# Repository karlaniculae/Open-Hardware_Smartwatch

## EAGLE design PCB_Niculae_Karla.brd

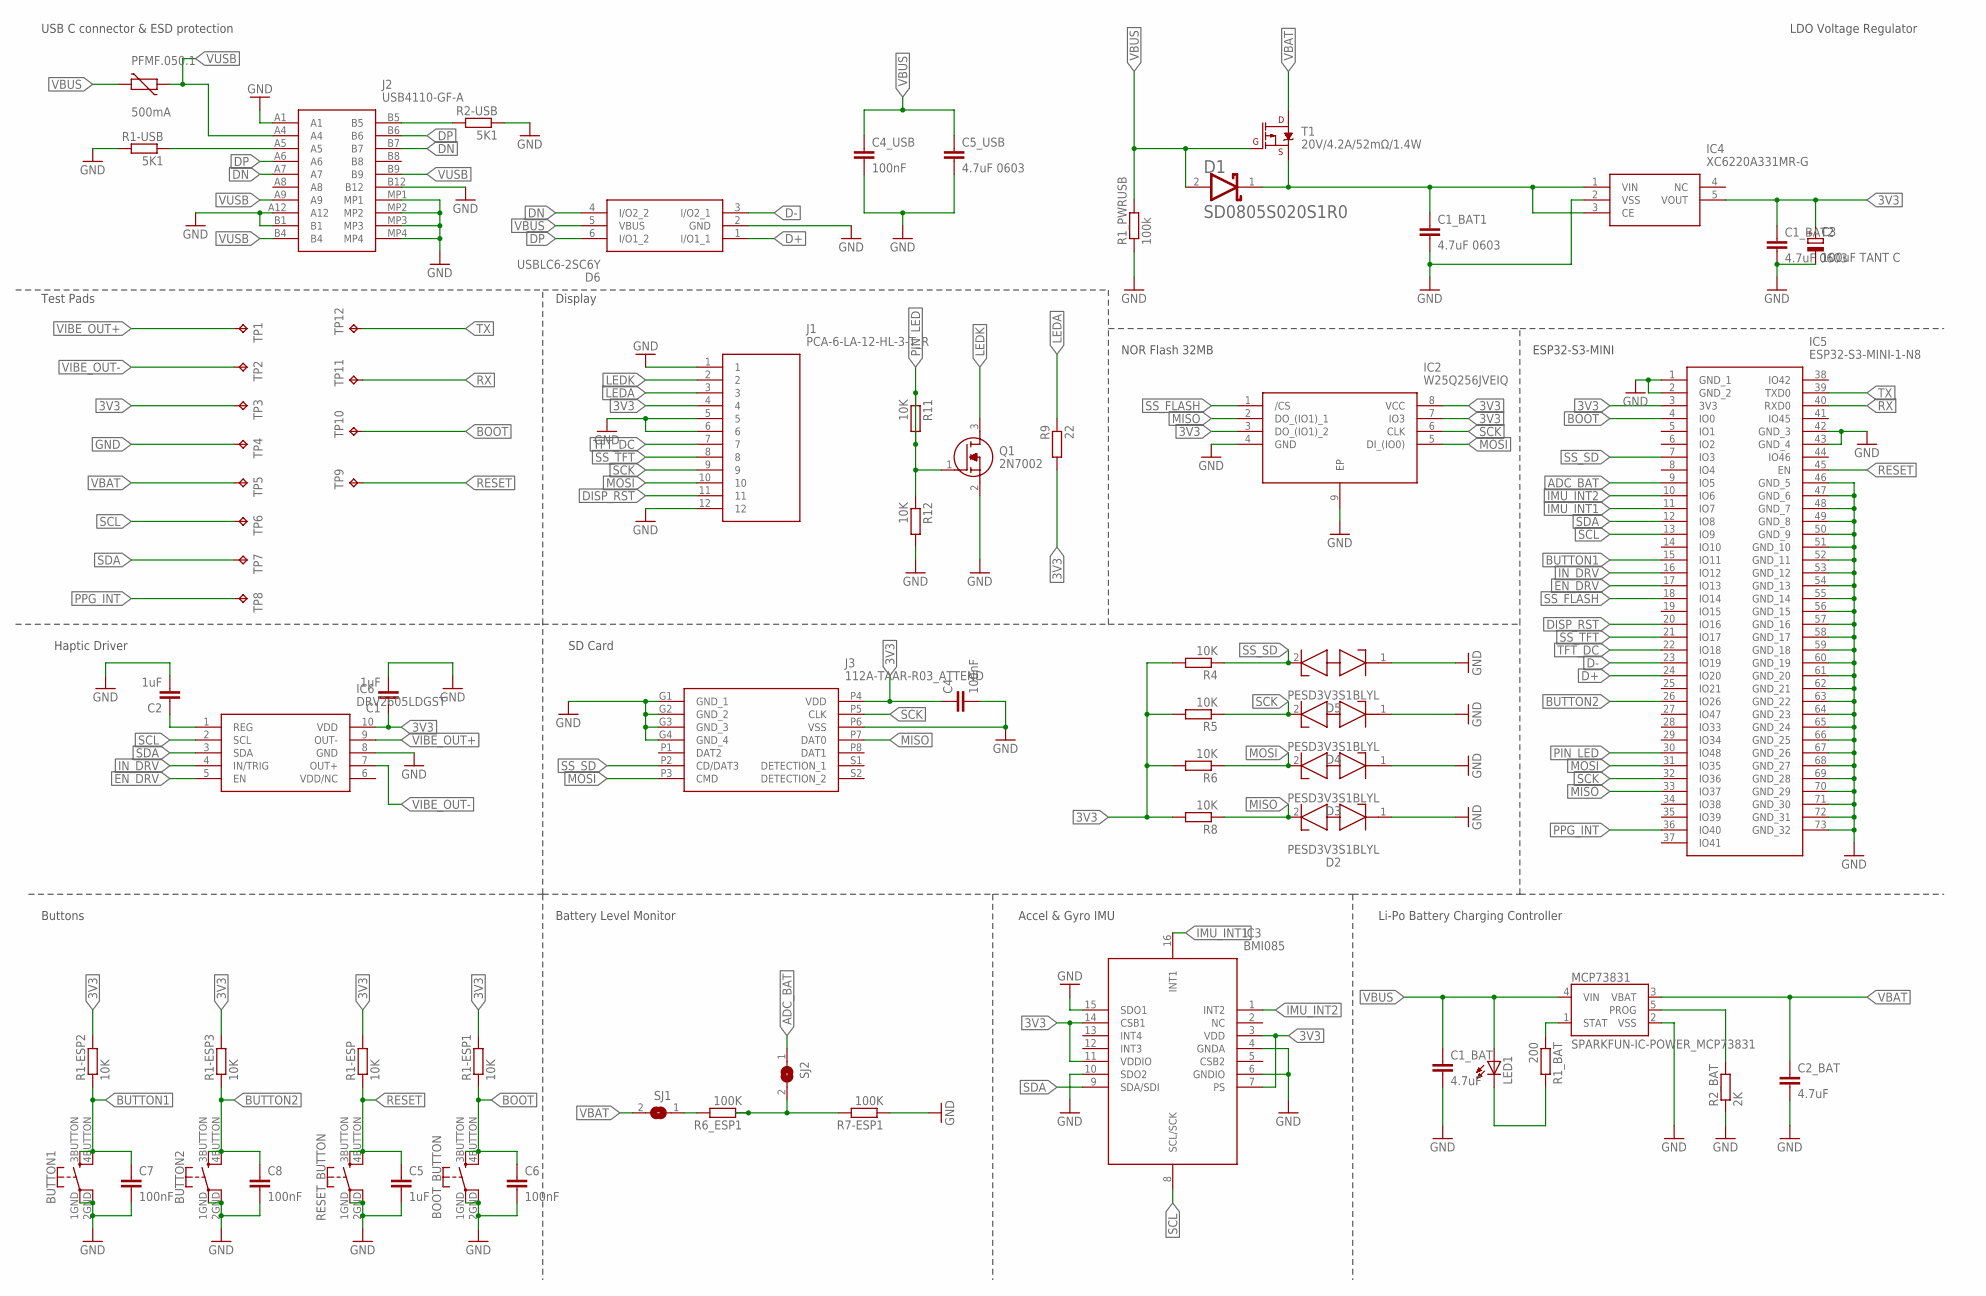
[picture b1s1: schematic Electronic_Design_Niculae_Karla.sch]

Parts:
BOOT_BUTTON: SPARKFUN-SWITCHES_MOMENTARY-SWITCH-SPST-2; BUTTON
BUTTON1, BUTTON2: SPARKFUN-SWITCHES_MOMENTARY-SWITCH-SPST-2; BUTTON
C1, C2, C5: 1uF; EAGLE-LTSPICE_C0402
C1_BAT, C2_BAT: 4.7uF; RCL_C0603
C1_BAT1, C1_BAT2, C5_USB: 4.7uF 0603; RCL_C0603
C3: 100uF TANT C; CT3528
C4, C6, C7, C8: 100nF; EAGLE-LTSPICE_C0402
C4_USB: 100nF; RCL_C0603
D1: AVX---SD0805S020S1R0_AVX_SD0805S020S1R0AVX_SD0805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; AVX---SD0805S020S1R0_AVX_SD0805S020S1R0_0
D2, D3, D4, D5: PESD3V3S1BLYL; PESD5V0S1BL315
D6: USBLC6-2SC6Y; SOT95P280X145-6N
IC2: W25Q256JVEIQ; SON127P800X600X80-9N
IC3: BMI085
IC4: XC6220A331MR-G; SOT95P280X120-5N
IC5: ESP32-S3-MINI-1-N8; ESP32S3MINI1N8
IC6: DRV2605LDGST; SOP50P490X110-10N
J1: PCA-6-LA-12-HL-3-T_R; PCA6LA12HL3TR
J2: USB4110-GF-A; USB4110GFA
J3: 112A-TAAR-R03_ATTEND; 112ATAARR03ATTEND
LED1: ADAFRUIT_LEDCHIP-LED0603; ADAFRUIT_CHIP-LED0603
MCP73831: SPARKFUN-IC-POWER_MCP73831; SPARKFUN-IC-POWER_SOT23-5
PFMF.050.1: 500mA; VARISTOR_CT/CN1812
Q1: 2N7002; SOT96P240X120-3N
R1-ESP, R1-ESP1, R1-ESP2, R1-ESP3, R4, R5, R6, R8, R11, R12: 10K; EAGLE-LTSPICE_R0402
R1-USB, R2-USB: 5K1; EAGLE-LTSPICE_R0402
R1_BAT: 200; EAGLE-LTSPICE_R0402
R1_PWRUSB: 100k; EAGLE-LTSPICE_R0402
R2_BAT: 2K; EAGLE-LTSPICE_R0402
R6_ESP1, R7-ESP1: 100K; EAGLE-LTSPICE_R0402
R9: 22; EAGLE-LTSPICE_R0402
RESET_BUTTON: SPARKFUN-SWITCHES_MOMENTARY-SWITCH-SPST-2; BUTTON
SJ1, SJ2: SJ
T1: 20V/4.2A/52mΩ/1.4W; SPARKFUN-DISCRETESEMI_SOT23-3
TP1, TP2, TP3, TP4, TP5, TP6, TP7, TP8, TP9, TP10, TP11, TP12: TPTP20R; TP20R

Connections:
3V3: C1.1, C1_BAT2.1, C3.+, C4.1, IC2.3 (DO_(IO1)_2), IC2.7 (IO3), IC2.8 (VCC), IC3.3 (VDD), IC3.7 (PS), IC3.11 (VDDIO), IC3.14 (CSB1), IC4.5 (VOUT), IC5.3 (3V3), IC6.10 (VDD), J1.4, J3.P4 (VDD), R1-ESP.2, R1-ESP1.2, R1-ESP2.2, R1-ESP3.2, R4.2, R5.2, R6.2, R8.2, R9.2, TP3.TP
ADC_BAT: IC5.9 (IO5), SJ2.1
BOOT: BOOT_BUTTON.3BUTTON (3), BOOT_BUTTON.4BUTTON (4), C6.1, IC5.4 (IO0), R1-ESP1.1, TP10.TP
BUTTON1: BUTTON1.3BUTTON (3), BUTTON1.4BUTTON (4), C7.1, IC5.15 (IO11), R1-ESP2.1
BUTTON2: BUTTON2.3BUTTON (3), BUTTON2.4BUTTON (4), C8.1, IC5.26 (IO26), R1-ESP3.1
D+: D6.1 (I/O1_1), IC5.24 (IO20)
D-: D6.3 (I/O2_1), IC5.23 (IO19)
DISP_RST: IC5.20 (IO16), J1.11
DN: D6.4 (I/O2_2), J2.A7, J2.B7
DP: D6.6 (I/O1_2), J2.A6, J2.B6
EN_DRV: IC5.17 (IO13), IC6.5 (EN)
GND: BOOT_BUTTON.1GND (1), BOOT_BUTTON.2GND (2), BUTTON1.1GND (1), BUTTON1.2GND (2), BUTTON2.1GND (1), BUTTON2.2GND (2), C1.2, C1_BAT.2, C1_BAT1.2, C1_BAT2.2, C2.2, C2_BAT.2, C3.-, C4.2, C4_USB.2, C5.2, C5_USB.2, C6.2, C7.2, C8.2, D2.1 (K1), D3.1 (K1), D4.1 (K1), D5.1 (K1), D6.2 (GND), IC2.4 (GND), IC2.9 (EP), IC3.4 (GNDA), IC3.6 (GNDIO), IC3.10 (SDO2), IC3.15 (SDO1), IC4.2 (VSS), IC5.1 (GND_1), IC5.2 (GND_2), IC5.42 (GND_3), IC5.43 (GND_4), IC5.46 (GND_5), IC5.47 (GND_6), IC5.48 (GND_7), IC5.49 (GND_8), IC5.50 (GND_9), IC5.51 (GND_10), IC5.52 (GND_11), IC5.53 (GND_12), IC5.54 (GND_13), IC5.55 (GND_14), IC5.56 (GND_15), IC5.57 (GND_16), IC5.58 (GND_17), IC5.59 (GND_18), IC5.60 (GND_19), IC5.61 (GND_20), IC5.62 (GND_21), IC5.63 (GND_22), IC5.64 (GND_23), IC5.65 (GND_24), IC5.66 (GND_25), IC5.67 (GND_26), IC5.68 (GND_27), IC5.69 (GND_28), IC5.70 (GND_29), IC5.71 (GND_30), IC5.72 (GND_31), IC5.73 (GND_32), IC6.8 (GND), J1.1, J1.5, J1.6, J1.12, J2.A1, J2.A12, J2.B1, J2.B12, J2.MP1, J2.MP2, J2.MP3, J2.MP4, J3.G1 (GND_1), J3.G2 (GND_2), J3.G3 (GND_3), J3.G4 (GND_4), J3.P6 (VSS), MCP73831.2 (VSS), Q1.2 (S), R1-USB.2, R1_PWRUSB.1, R2-USB.1, R2_BAT.1, R7-ESP1.1, R12.2, RESET_BUTTON.1GND (1), RESET_BUTTON.2GND (2), TP4.TP
IMU_INT1: IC3.16 (INT1), IC5.11 (IO7)
IMU_INT2: IC3.1 (INT2), IC5.10 (IO6)
IN_DRV: IC5.16 (IO12), IC6.4 (IN/TRIG)
LEDA: J1.3, R9.1
LEDK: J1.2, Q1.3 (D)
MISO: D2.2 (K2), IC2.2 (DO_(IO1)_1), IC5.33 (IO37), J3.P7 (DAT0), R8.1
MOSI: D3.2 (K2), IC2.5 (DI_(IO0)), IC5.31 (IO35), J1.10, J3.P3 (CMD), R6.1
unnamed: J2.B5, R2-USB.2
unnamed: R6_ESP1.1, R7-ESP1.2, SJ2.2
unnamed: C1_BAT1.1, D1.1 (CATHODE), IC4.1 (VIN), IC4.3 (CE), T1.2 (S)
unnamed: J2.A5, R1-USB.1
unnamed: R6_ESP1.2, SJ1.1
unnamed: C2.1, IC6.1 (REG)
unnamed: MCP73831.1 (STAT), R1_BAT.1
unnamed: MCP73831.5 (PROG), R2_BAT.2
unnamed: LED1.C, R1_BAT.2
PIN_LED: IC5.30 (IO48), Q1.1 (G), R11.1, R11.2, R12.1
PPG_INT: IC5.36 (IO40), TP8.TP
RESET: C5.1, IC5.45 (EN), R1-ESP.1, RESET_BUTTON.3BUTTON (3), RESET_BUTTON.4BUTTON (4), TP9.TP
RX: IC5.40 (RXD0), TP11.TP
SCK: D4.2 (K2), IC2.6 (CLK), IC5.32 (IO36), J1.9, J3.P5 (CLK), R5.1
SCL: IC3.8 (SCL/SCK), IC5.13 (IO9), IC6.2 (SCL), TP6.TP
SDA: IC3.9 (SDA/SDI), IC5.12 (IO8), IC6.3 (SDA), TP7.TP
SS_FLASH: IC2.1 (/CS), IC5.18 (IO14)
SS_SD: D5.2 (K2), IC5.7 (IO3), J3.P2 (CD/DAT3), R4.1
SS_TFT: IC5.21 (IO17), J1.8
TFT_DC: IC5.22 (IO18), J1.7
TX: IC5.39 (TXD0), TP12.TP
VBAT: C2_BAT.1, MCP73831.3 (VBAT), SJ1.2, T1.3 (D), TP5.TP
VBUS: C1_BAT.1, C4_USB.1, C5_USB.1, D1.2 (ANODE), D6.5 (VBUS), LED1.A, MCP73831.4 (VIN), PFMF.050.1.2, R1_PWRUSB.2, T1.1 (G)
VIBE_OUT+: IC6.9 (OUT-), TP1.TP
VIBE_OUT-: IC6.7 (OUT+), TP2.TP
VUSB: J2.A4, J2.A9, J2.B4, J2.B9, PFMF.050.1.1

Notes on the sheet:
USB C connector & ESD protection
LDO Voltage Regulator
Test Pads
Display
NOR Flash 32MB
ESP32-S3-MINI
Haptic Driver
SD Card
Li-Po Battery Charging Controller
Accel & Gyro IMU
Battery Level Monitor
Buttons

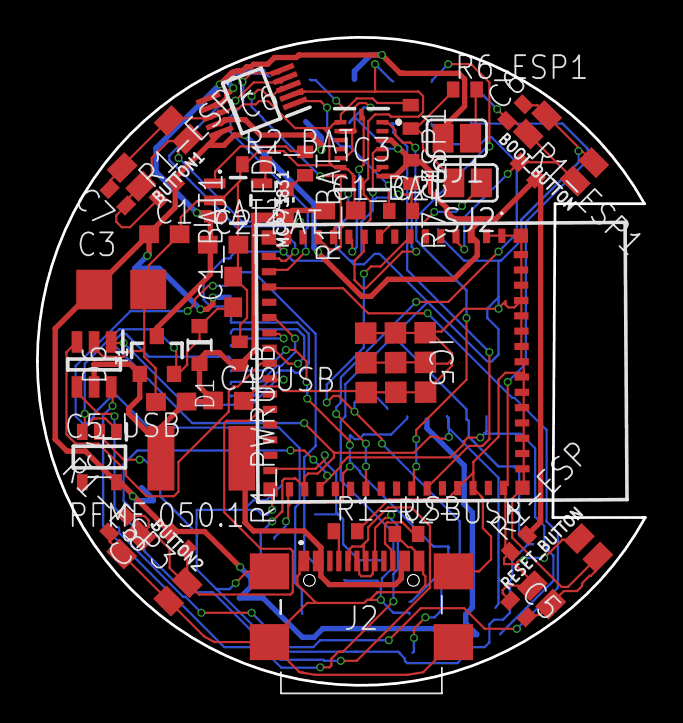
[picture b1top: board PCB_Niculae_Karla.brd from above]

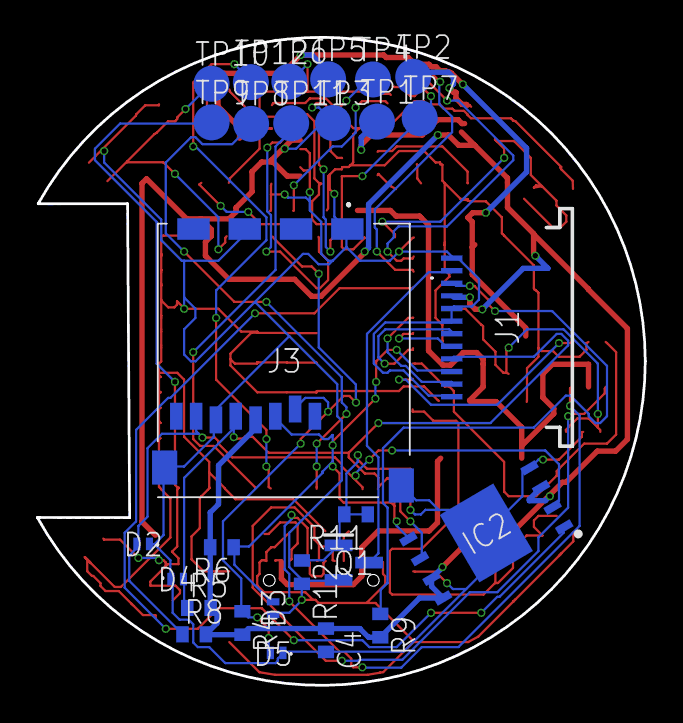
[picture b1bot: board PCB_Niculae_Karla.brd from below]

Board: 2 copper layers, 33.8 x 36.0 mm, 69 parts (28 on the bottom side), 45 nets.

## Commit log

2024-10-21 Create TaskDetails
